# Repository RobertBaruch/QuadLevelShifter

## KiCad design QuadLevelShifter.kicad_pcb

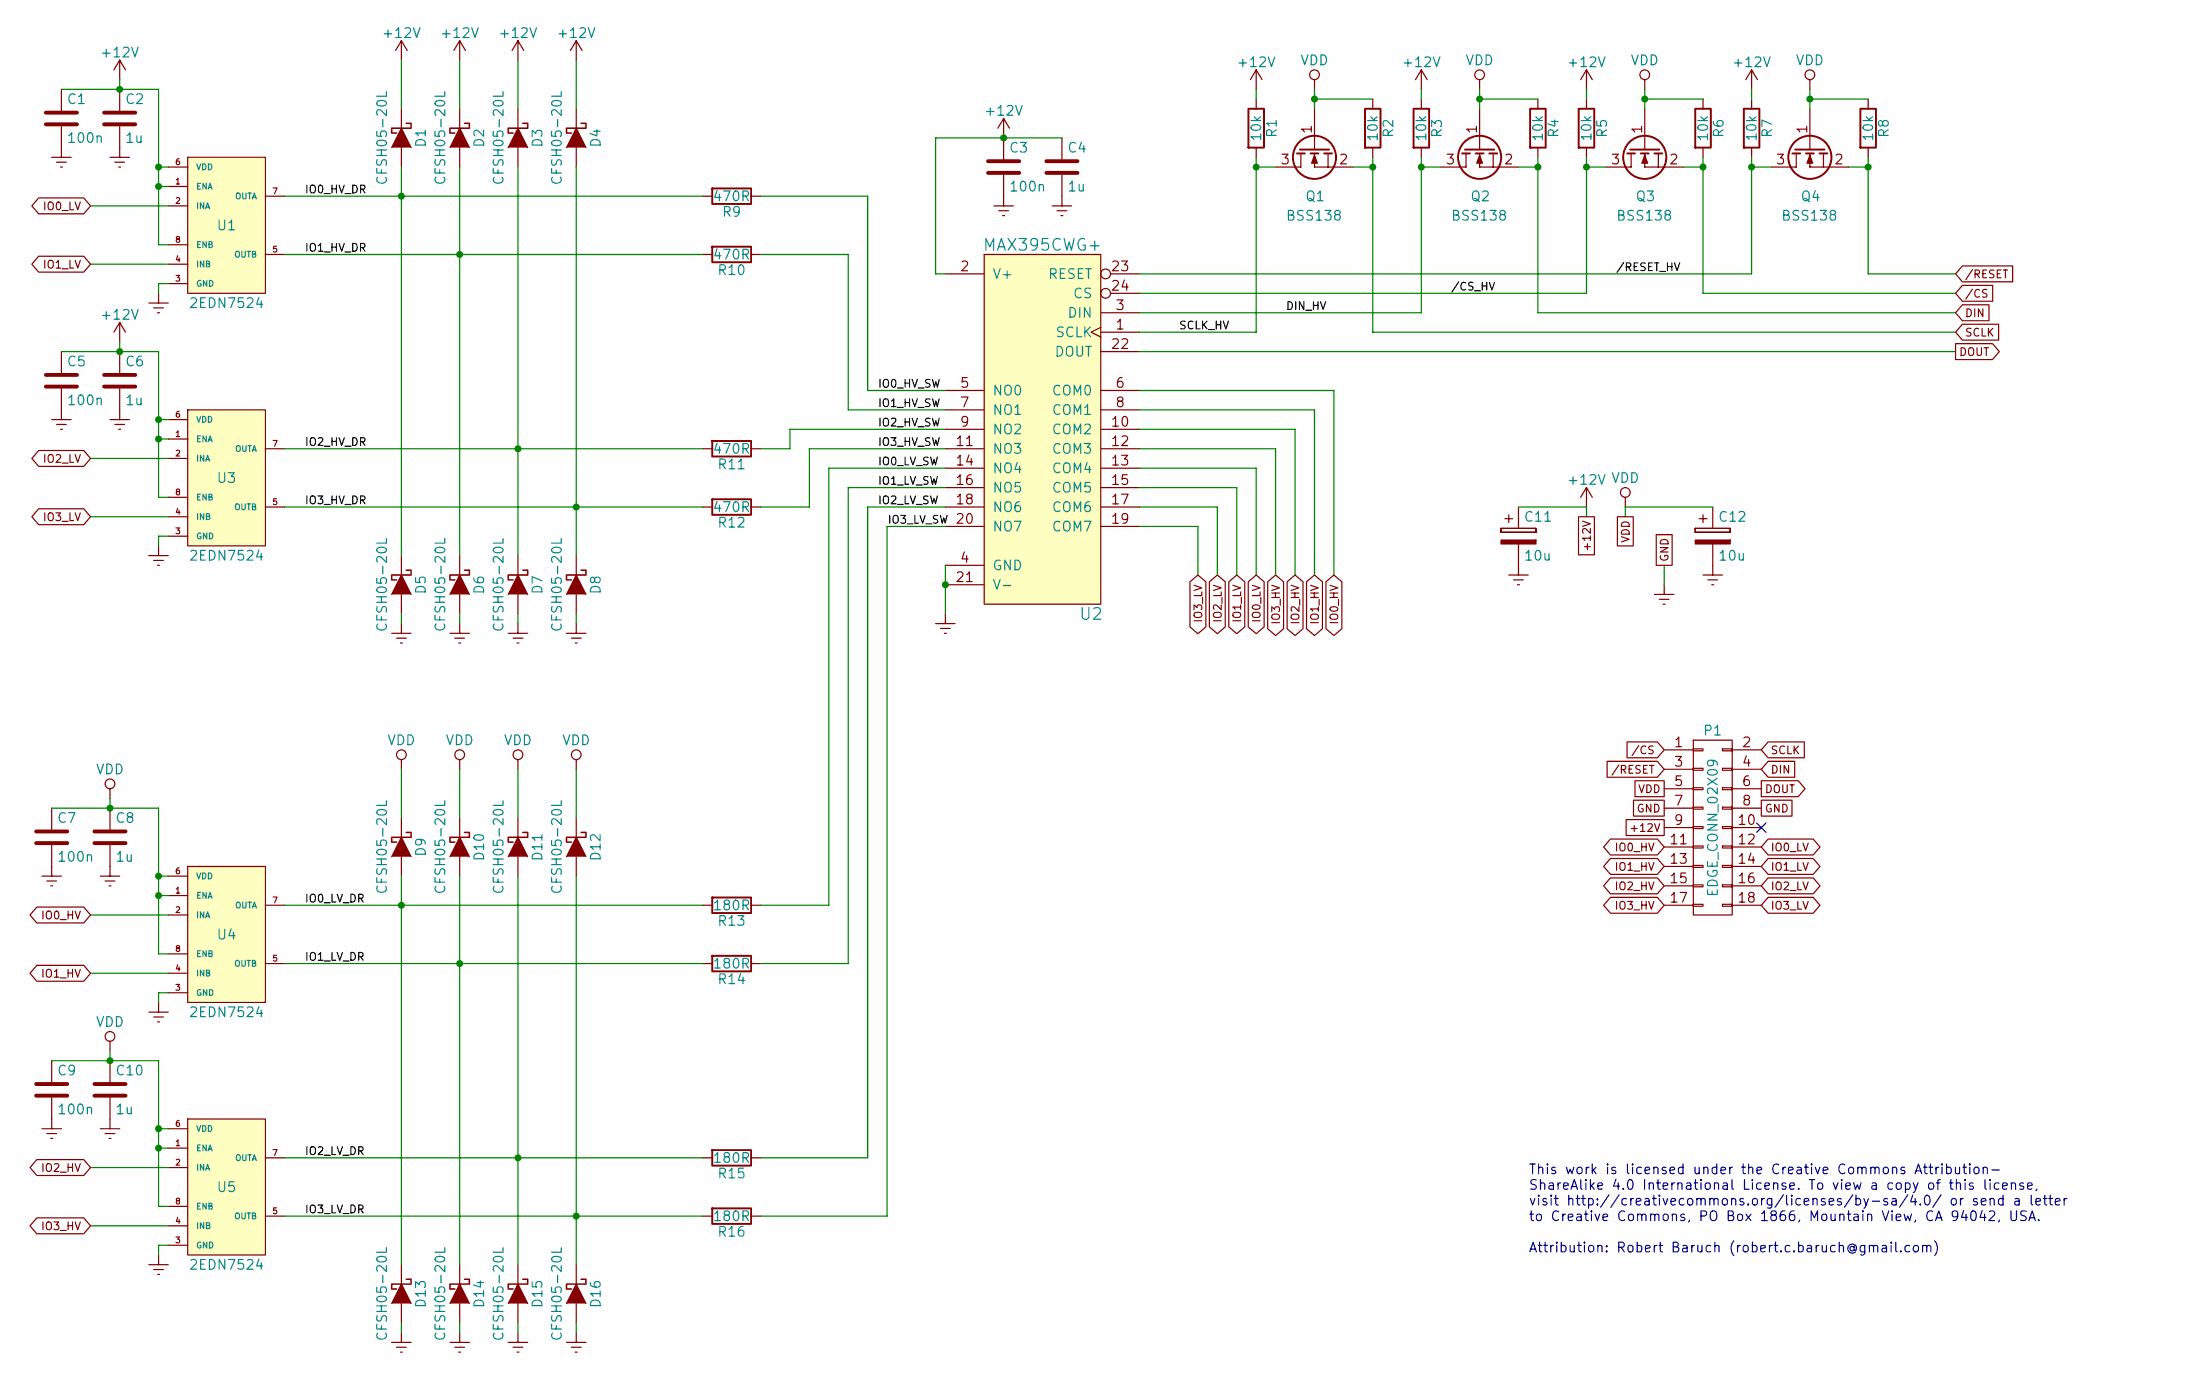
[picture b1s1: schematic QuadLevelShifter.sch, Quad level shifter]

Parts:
C1, C3, C5, C7, C9: 100n; C_0805; MFG P/N CGJ4J2X7R1E104K125AA
C2, C4, C6, C8, C10: 1u; C_0805; MFG P/N C2012X5R1E105M085AC
C11, C12: 10u; c_elec_6.3x5.3; MFG P/N UWX1H100MCL1GB
D1, D2, D3, D4, D5, D6, D7, D8, D9, D10, D11, D12, D13, D14, D15, D16: CFSH05-20L; SOD-882L; MFG P/N CFSH05-20L TR
P1: EDGE_CONN_02X09; MFG P/N CES-109-01-T-D
Q1, Q2, Q3, Q4: BSS138; SOT-23; MFG P/N BSS138
R1, R2, R3, R4, R5, R6, R7, R8: 10k; R_0805; MFG P/N RC0805FR-0710KL
R9, R10, R11, R12: 470R; R_1210; MFG P/N CRCW1210470RFKEA
R13, R14, R15, R16: 180R; R_1210; MFG P/N CRCW1206180RFKEA
U1, U3, U4, U5: 2EDN7524; SOIC-8_3.9x4.9mm_Pitch1.27mm; MFG P/N 2EDN7524FXTMA1
U2: MAX395CWG+; SOIC-24-W; MFG P/N MAX395CWG+

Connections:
+12V: C1.1, C2.1, C3.1, C4.1, C5.1, C6.1, C11.1, D1.1 (K), D2.1 (K), D3.1 (K), D4.1 (K), P1.9, R1.1, R3.1, R5.1, R7.1, U1.1 (ENA), U1.6 (VDD), U1.8 (ENB), U2.2 (V+), U3.1 (ENA), U3.6 (VDD), U3.8 (ENB)
//CS_HV: Q3.3 (D), R5.2, U2.24 (CS)
//RESET_HV: Q4.3 (D), R7.2, U2.23 (RESET)
/CS: P1.1, Q3.2 (S), R6.2
/DIN_HV: Q2.3 (D), R3.2, U2.3 (DIN)
/IO0_HV_DR: D1.2 (A), D5.1 (K), R9.2, U1.7 (OUTA)
/IO0_HV_SW: R9.1, U2.5 (NO0)
/IO0_LV_DR: D9.2 (A), D13.1 (K), R13.2, U4.7 (OUTA)
/IO0_LV_SW: R13.1, U2.14 (NO4)
/IO1_HV_DR: D2.2 (A), D6.1 (K), R10.2, U1.5 (OUTB)
/IO1_HV_SW: R10.1, U2.7 (NO1)
/IO1_LV_DR: D10.2 (A), D14.1 (K), R14.2, U4.5 (OUTB)
/IO1_LV_SW: R14.1, U2.16 (NO5)
/IO2_HV_DR: D3.2 (A), D7.1 (K), R11.2, U3.7 (OUTA)
/IO2_HV_SW: R11.1, U2.9 (NO2)
/IO2_LV_DR: D11.2 (A), D15.1 (K), R15.2, U5.7 (OUTA)
/IO2_LV_SW: R15.1, U2.18 (NO6)
/IO3_HV_DR: D4.2 (A), D8.1 (K), R12.2, U3.5 (OUTB)
/IO3_HV_SW: R12.1, U2.11 (NO3)
/IO3_LV_DR: D12.2 (A), D16.1 (K), R16.2, U5.5 (OUTB)
/IO3_LV_SW: R16.1, U2.20 (NO7)
/RESET: P1.3, Q4.2 (S), R8.2
/SCLK_HV: Q1.3 (D), R1.2, U2.1 (SCLK)
DIN: P1.4, Q2.2 (S), R4.2
DOUT: P1.6, U2.22 (DOUT)
GND: C1.2, C2.2, C3.2, C4.2, C5.2, C6.2, C7.2, C8.2, C9.2, C10.2, C11.2, C12.2, D5.2 (A), D6.2 (A), D7.2 (A), D8.2 (A), D13.2 (A), D14.2 (A), D15.2 (A), D16.2 (A), P1.7, P1.8, U1.3 (GND), U2.4 (GND), U2.21 (V-), U3.3 (GND), U4.3 (GND), U5.3 (GND)
IO0_HV: P1.11, U2.6 (COM0), U4.2 (INA)
IO0_LV: P1.12, U1.2 (INA), U2.13 (COM4)
IO1_HV: P1.13, U2.8 (COM1), U4.4 (INB)
IO1_LV: P1.14, U1.4 (INB), U2.15 (COM5)
IO2_HV: P1.15, U2.10 (COM2), U5.2 (INA)
IO2_LV: P1.16, U2.17 (COM6), U3.2 (INA)
IO3_HV: P1.17, U2.12 (COM3), U5.4 (INB)
IO3_LV: P1.18, U2.19 (COM7), U3.4 (INB)
SCLK: P1.2, Q1.2 (S), R2.2
VDD: C7.1, C8.1, C9.1, C10.1, C12.1, D9.1 (K), D10.1 (K), D11.1 (K), D12.1 (K), P1.5, Q1.1 (G), Q2.1 (G), Q3.1 (G), Q4.1 (G), R2.1, R4.1, R6.1, R8.1, U4.1 (ENA), U4.6 (VDD), U4.8 (ENB), U5.1 (ENA), U5.6 (VDD), U5.8 (ENB)

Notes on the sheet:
This work is licensed under the Creative Commons Attribution- ShareAlike 4.0 International License. To view a copy of this license, visit http://creativecommons.org/licenses/by-sa/4.0/ or send a letter to Creative Commons, PO Box 1866, Mountain View, CA 94042, USA. Attribution: Robert Baruch (rober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

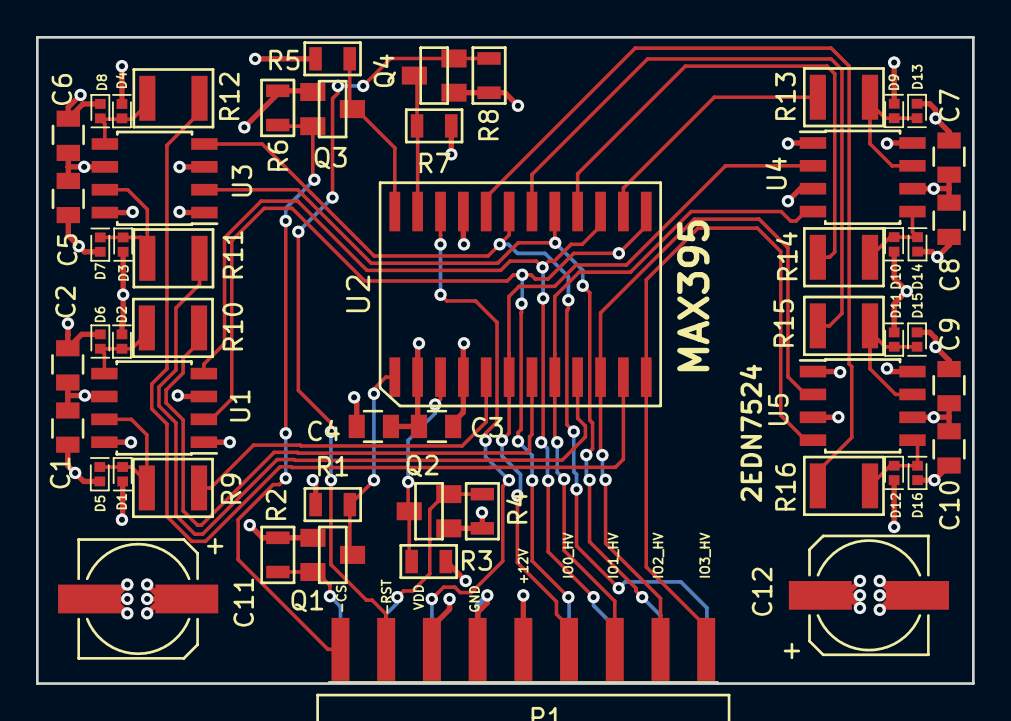
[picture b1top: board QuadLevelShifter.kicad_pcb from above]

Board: 4 copper layers, 52.0 x 35.9 mm, 54 parts (0 on the bottom side), 36 nets.

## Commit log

2016-12-05 Almost done
2016-12-05 First attempt at PCB
2016-12-09 Completed revision A
